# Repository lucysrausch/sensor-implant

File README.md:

# sensor-implant
WIP hardware design files for a sensor implant for my bachelors thesis.

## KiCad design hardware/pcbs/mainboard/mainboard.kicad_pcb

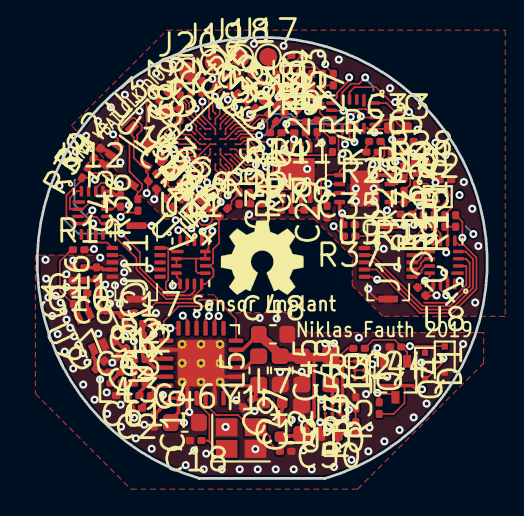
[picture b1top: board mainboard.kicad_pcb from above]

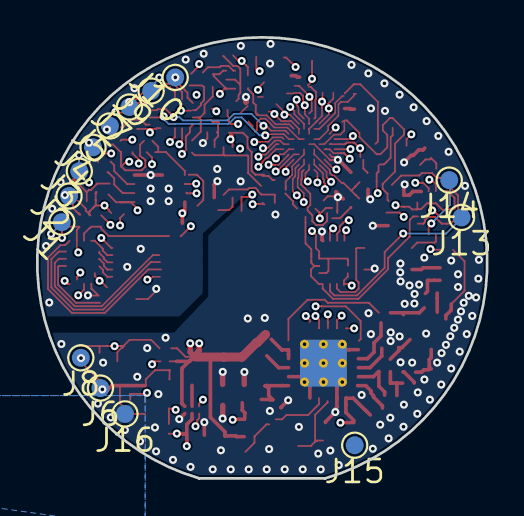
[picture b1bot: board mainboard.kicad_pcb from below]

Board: 4 copper layers, 25.0 x 24.5 mm, 142 parts (14 on the bottom side), 107 nets.

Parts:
C1, C15, C20, C21, C22, C23, C25, C26, C27, C29, C30, C31, C32, C38, C39, C40: 1n; C_0201_0603Metric
C2, C5, C24, C28, C34, C35, C37, C41, C42, C43, C44: 100n; C_0201_0603Metric
C3: 3p; C_0201_0603Metric
C4: 12p; C_0201_0603Metric
C6: 6.8p; C_0201_0603Metric
C7: DNP; C_0201_0603Metric
C8: 22p; C_0201_0603Metric
C9, C13, C16: 1u; C_0201_0603Metric
C10, C11: 3.3p; C_0201_0603Metric
C12, C17: 1.8p; C_0201_0603Metric
C14: 1p; C_0201_0603Metric
C18, C19: 18p; C_0201_0603Metric
C33, C36, C50: 1u; C_0402_1005Metric
C45, C46, C47, C48, C49: 10u; C_0603_1608Metric
D1: D; D_SC-80
D2: D_TVS; D_SC-80
J1, J2, J3, J4, J5, J6, J7, J8, J9, J10, J13, J14, J15, J16, J17, J18, J19, J20: PAD; TestPoint_Pad_D1.0mm
J11, J12: Conn_02x05_Odd_Even_MountingPin; DF37NB10DS04V53
L1: 47n; L_0201_0603Metric
L2: FERRET; L_0402_1005Metric
L3: 2.7n; L_0201_0603Metric
L4, L6: 9.1n; L_0201_0603Metric
L5: 15u; L_0603_1608Metric
L7: DNP; L_0402_1005Metric
L8: 18n; L_0201_0603Metric
L9: 2u2; L_0603_1608Metric
Q1, Q2, Q3: CSD75208W1015; WLCSP-6_1.4x1.0mm_P0.4mm
Q4: 2N7002; SOT-323_SC-70
R1, R2, R3, R5, R8, R10, R14, R15, R16, R18, R19, R23, R27, R30, R33, R36, R37, R38: 100; R_0201_0603Metric
R4, R11, R17, R26, R34, R35, R39, R42: 10k; R_0201_0603Metric
R6, R9, R12, R21, R25, R28: 200k; R_0201_0603Metric
R7, R13, R22, R29, R40: 2k; R_0201_0603Metric
R20, R24, R31, R32: 10M; R_0201_0603Metric
R41, R43: DNP; R_0201_0603Metric
U1: SX1261; QFN-24-1EP_4x4mm_P0.5mm_EP2.6x2.6mm_ThermalVias
U2: PE4259; SOT-363_SC-70-6
U3: REF3020; SOT-323_SC-70
U4: STM32L072CBYx; ST_WLCSP-49_Die447
U5, U8, U11, U12: TMUX1209; QFN40P260X180X55-16N
U6, U9: LPV542; WSON-8-1EP_3x3mm_P0.5mm_EP1.6x2.0mm
U7: LMT70; WLCSP-4_1.0x1.0mm_P0.4mm
U10: TPS61099; WLCSP-6_1.4x1.0mm_P0.4mm_hdi
U13: OPA333xxDCK; SOT-353_SC-70-5
Y1: 32MHz; Crystal_SMD_EuroQuartz_X22-4Pin_2.5x2.0mm

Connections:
+5VA: C24.1, C33.1, C34.1, C35.1, C42.1, C43.1, C50.1, R34.1, U3.1, U5.12, U5.16, U6.8, U7.A2, U8.12, U8.16, U9.8, U10.B2, U11.2, U11.3, U11.9, U11.11, U11.12, U12.2, U12.11, U12.12, U12.16, U13.5
+BATT: J6.1, Q3.B1, Q3.B2, Q3.C1, R31.1
ADC_IN0: C22.1, R10.2, U4.E5
ADC_IN1: C23.1, R14.2, U4.E4
ADC_IN2: C25.1, R15.2, U4.F6
ADC_IN3: C26.1, R27.2, U4.G7
ADC_IN6: C39.1, R19.2, U4.G5
ADC_IN7: C30.1, R37.2, U4.F4
ADC_IN8: C31.1, R30.2, U4.G4
ADC_IN9: C32.1, R38.2, U4.D3
ADC_IN10: C38.1, R36.2, U4.C5
ADC_IN11: C28.1, R20.2, R24.1, R40.1, U4.C4
ADC_IN12: C40.1, R33.2, U4.E7
AFE_EN: U4.E1, U10.C1
ANT_SW: R1.2, U4.B7
COIL: D1.2, J8.1
DAC_OUT1: R12.2, R28.2, U4.F5
DAC_OUT2: U4.G6, U13.1
DIO2: R2.1, U1.12
ELEC1: J11.9, U11.6
ELEC2: J13.1, U11.7
ELEC_SNS1: R36.1, U11.4, U11.5, U12.3
ELEC_SNS2: R38.1, U11.8, U11.10, U12.10
GNDD: C1.2, C2.2, C5.2, C6.2, C7.2, C9.2, C10.2, C11.2, C13.2, C14.2, C15.2, C16.2, C17.2, C18.2, C19.2, C21.1, C22.2, C23.2, C24.2, C25.2, C26.2, C28.2, C29.1, C30.2, C31.2, C32.2, C33.2, C34.2, C35.2, C36.2, C37.2, C38.2, C39.2, C40.2, C41.2, C42.2, C43.2, C44.2, C45.2, C46.2, C47.2, C48.2, C49.2, C50.2, D2.2, J11.2, J11.3, J11.6, J11.MP, J12.10, J12.MP, J16.1, J20.1, Q4.2, R6.2, R21.2, R24.2, R35.2, R42.2, U1.2, U1.5, U1.8, U1.20, U1.25, U2.2, U3.3, U4.A5, U4.D4, U5.13, U6.4, U7.A1, U8.13, U9.4, U10.A2, U11.13, U12.13, U13.2, Y1.2, Y1.4
ISFET1_D: R17.1, R23.1, R37.1, U8.7
ISFET1_D1: J12.1, U8.11
ISFET1_D2: J12.3, U8.10
ISFET1_D3: J12.5, U8.9
ISFET1_D4: J12.7, U8.8
ISFET1_S: C27.1, J12.9, R10.1, R26.2, R29.1, U9.7
ISFET1_SHNT: Q2.A1, Q2.A2, Q2.C1, R19.1, R23.2, R43.1
ISFET2_D: R4.1, R8.1, R27.1, U5.7
ISFET2_D2: J1.1, U5.10
ISFET2_D3: J2.1, U5.9
ISFET2_D4: J3.1, U5.8
ISFET2_S: C20.1, J4.1, R11.2, R13.1, R14.1, U6.7
ISFET2_SHNT: Q1.A1, Q1.A2, Q1.C1, R8.2, R30.1, R41.1
MUX1IN0: U4.F2, U8.15
MUX1IN1: U4.G1, U8.14
MUX2IN0: U4.G3, U5.15
MUX2IN1: U4.F3, U5.14
MUX3EN: U4.E2, U11.16
MUX3IN0: U4.C7, U11.15
MUX3IN1: U4.C1, U11.14
MUX4IN0: U4.A6, U12.15
MUX4IN1: U4.B5, U12.14
unnamed: C1.1, R1.1, U2.6
unnamed: C2.1, L1.1, U1.24
unnamed: C3.1, C4.2, C6.1, L3.2
unnamed: C3.2, L1.2, L3.1, U1.23
unnamed: C4.1, L4.1
unnamed: C5.1, U4.D5
unnamed: C7.1, L4.2, U2.1
unnamed: C8.2, U2.5
unnamed: C9.1, L5.1, L7.1, U1.7
unnamed: C8.1, C10.1, L6.1
unnamed: C12.1, C14.1, U2.3
unnamed: C12.2, L8.1, U1.22
unnamed: C13.1, U3.2, U4.E6
unnamed: C15.1, R2.2, U2.4
unnamed: C16.1, C46.1, L2.1, L7.2, U1.1
unnamed: C17.1, L8.2, U1.21
unnamed: C18.1, U1.3, Y1.1
unnamed: C19.1, U1.4, Y1.3
unnamed: C20.2, R4.2, U6.6
unnamed: C21.2, R9.2, R11.1, U6.5
unnamed: C27.2, R17.2, U9.6
unnamed: C29.2, R25.2, R26.1, U9.5
unnamed: L5.2, U1.9
unnamed: L9.2, U10.B1
unnamed: Q1.B1, Q1.B2, R3.1, R41.2
unnamed: Q1.C2, R5.2
unnamed: Q2.B1, Q2.B2, R16.1, R43.2
unnamed: Q2.C2, R18.2
unnamed: Q3.A2, Q4.3, R31.2
unnamed: R3.2, R7.1, R9.1, U6.1
unnamed: R6.1, R7.2, U6.2
unnamed: R12.1, R13.2, U6.3
unnamed: R16.2, R22.1, R25.1, U9.1
unnamed: R21.1, R22.2, U9.2
unnamed: R28.1, R29.2, U9.3
unnamed: R34.2, R35.1, U10.C2
unnamed: R39.2, R42.1, U13.3
unnamed: R40.2, U7.B1
O2_ELEC1: J11.10, U12.6
O2_ELEC2: J14.1, U12.7
O2_FORCE: R39.1, U12.4, U12.9, U13.4
REFFET1_D: J12.2, R15.1, R18.1, U8.6
REFFET1_D2: J12.8, U8.3
REFFET1_D3: J12.6, U8.4
REFFET1_D4: J12.4, U8.5
REFFET2_D: J5.1, R5.1, R33.1, U5.6
REFFET2_D2: J7.1, U5.3
REFFET2_D3: J9.1, U5.4
REFFET2_D4: J10.1, U5.5
RF_ANT: C11.1, J11.4, L6.2
RF_BUSY: U1.14, U4.D2
RF_CS: U1.19, U4.A2
RF_MISO: U1.16, U4.B3
RF_MOSI: U1.17, U4.A4
RF_RST: U1.15, U4.D1
RF_SCK: U1.18, U4.A3
SWCLK: J18.1, U4.B2
SWDIO: J17.1, U4.C2
TAG_EN: C44.1, D1.1, D2.1, Q4.1, R32.1, U4.F1
T_EN: U4.B1, U7.B2
VCC: C36.1, C37.1, C41.1, C45.1, C47.1, C48.1, C49.1, J19.1, L2.2, L9.1, Q3.A1, R20.1, R32.2, U1.10, U1.11, U4.A7, U4.B6, U4.F7, U4.G2, U10.A1

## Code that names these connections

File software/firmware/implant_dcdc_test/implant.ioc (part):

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Mcu.Name=STM32L072C(B-Z)Yx
Mcu.Package=WLCSP49
Mcu.UserName=STM32L072CBYx
PA0.Mode=IN0
PA0.Signal=ADC_IN0
PA1.Mode=IN1
PA1.Signal=ADC_IN1
PA10.GPIOParameters=GPIO_Label
PA10.GPIO_Label=MUX3IN1
PA10.Signal=GPIO_Output
PA11.GPIOParameters=GPIO_Label
PA11.GPIO_Label=BUSY
PA11.Signal=GPIO_Input
PA12.GPIOParameters=GPIO_Label
PA12.GPIO_Label=TEMPEN
PA12.Signal=GPIO_Output
PA13.Mode=Serial_Wire
PA13.Signal=SYS_SWDIO
PA14.Mode=Serial_Wire
PA14.Signal=SYS_SWCLK
PA15.Mode=NSS_Signal_Hard_Output
PA15.Signal=SPI1_NSS
PA2.Mode=IN2
PA2.Signal=ADC_IN2
PA3.Mode=IN3
PA3.Signal=ADC_IN3
PA4.Signal=COMP_DAC1_group
PA5.Signal=COMP_DAC2_group
PA6.Mode=IN6
PA6.Signal=ADC_IN6
PA7.Mode=IN7
PA7.Signal=ADC_IN7
PA8.GPIOParameters=GPIO_Label
PA8.GPIO_Label=RESET
PA8.Signal=GPIO_Output
PA9.GPIOParameters=GPIO_Label
PA9.GPIO_Label=MUX3EN
PA9.Signal=GPIO_Output
PB0.Mode=IN8
PB0.Signal=ADC_IN8
PB1.Mode=IN9
PB1.Signal=ADC_IN9
PB10.GPIOParameters=GPIO_Label
PB10.GPIO_Label=MUX2IN0
PB10.Signal=GPIO_Output
PB11.GPIOParameters=GPIO_Label
PB11.GPIO_Label=MUX2IN1
PB11.Signal=GPIO_Output
PB12.GPIOParameters=GPIO_Label
PB12.GPIO_Label=MUX1IN1
PB12.Signal=GPIO_Output
PB13.GPIOParameters=GPIO_Label
PB13.GPIO_Label=MUX1IN0
PB13.Signal=GPIO_Output
PB14.GPIOParameters=PinState,GPIO_Label,GPIO_ModeDefaultOutputPP
PB14.GPIO_Label=TAGEN
PB14.GPIO_ModeDefaultOutputPP=GPIO_MODE_OUTPUT_OD
PB14.PinState=GPIO_PIN_SET
PB14.Signal=GPIO_Output
PB15.GPIOParameters=GPIO_Label
PB15.GPIO_Label=AFEEN
PB15.Signal=GPIO_Output
PB3.Mode=Full_Duplex_Master
PB3.Signal=SPI1_SCK
PB4.Mode=Full_Duplex_Master
PB4.Signal=SPI1_MISO
PB5.Mode=Full_Duplex_Master
PB5.Signal=SPI1_MOSI
PB8.GPIOParameters=GPIO_Label
PB8.GPIO_Label=MUX4IN1
PB8.Signal=GPIO_Output
PB9.GPIOParameters=GPIO_Label
PB9.GPIO_Label=MUX4IN0
PB9.Signal=GPIO_Output
PC0.Mode=IN10
PC0.Signal=ADC_IN10
PC1.Mode=IN11
PC1.Signal=ADC_IN11
PC13.GPIOParameters=GPIO_Label
PC13.GPIO_Label=ANTSW
PC13.Signal=GPIO_Output
PC15-OSC32_OUT.GPIOParameters=GPIO_Label
PC15-OSC32_OUT.GPIO_Label=MUX3IN0
PC15-OSC32_OUT.Signal=GPIO_Output
PC2.Mode=IN12
PC2.Signal=ADC_IN12
RCC.HSE_VALUE=8000000
RCC.SYSCLKFreq_VALUE=4000000
RCC.SYSCLKSource=RCC_SYSCLKSOURCE_HSI
board=implant

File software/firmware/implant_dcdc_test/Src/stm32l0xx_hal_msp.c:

/**
  ******************************************************************************
  * File Name          : stm32l0xx_hal_msp.c
  * Description        : This file provides code for the MSP Initialization 
  *                      and de-Initialization codes.
  ******************************************************************************
  ** This notice applies to any and all portions of this file
  * that are not between comment pairs USER CODE BEGIN and
  * USER CODE END. Other portions of this file, whether 
  * inserted by the user or by software development tools
  * are owned by their respective copyright owners.
  *
  * COPYRIGHT(c) 2019 STMicroelectronics
  *
  * Redistribution and use in source and binary forms, with or without modification,
  * are permitted provided that the following conditions are met:
  *   1. Redistributions of source code must retain the above copyright notice,
  *      this list of conditions and the following disclaimer.
  *   2. Redistributions in binary form must reproduce the above copyright notice,
  *      this list of conditions and the following disclaimer in the documentation
  *      and/or other materials provided with the distribution.
  *   3. Neither the name of STMicroelectronics nor the names of its contributors
  *      may be used to endorse or promote products derived from this software
  *      without specific prior written permission.
  *
  * THIS SOFTWARE IS PROVIDED BY THE COPYRIGHT HOLDERS AND CONTRIBUTORS "AS IS"
  * AND ANY EXPRESS OR IMPLIED WARRANTIES, INCLUDING, BUT NOT LIMITED TO, THE
  * IMPLIED WARRANTIES OF MERCHANTABILITY AND FITNESS FOR A PARTICULAR PURPOSE ARE
  * DISCLAIMED. IN NO EVENT SHALL THE COPYRIGHT HOLDER OR CONTRIBUTORS BE LIABLE
  * FOR ANY DIRECT, INDIRECT, INCIDENTAL, SPECIAL, EXEMPLARY, OR CONSEQUENTIAL
  * DAMAGES (INCLUDING, BUT NOT LIMITED TO, PROCUREMENT OF SUBSTITUTE GOODS OR
  * SERVICES; LOSS OF USE, DATA, OR PROFITS; OR BUSINESS INTERRUPTION) HOWEVER
  * CAUSED AND ON ANY THEORY OF LIABILITY, WHETHER IN CONTRACT, STRICT LIABILITY,
  * OR TORT (INCLUDING NEGLIGENCE OR OTHERWISE) ARISING IN ANY WAY OUT OF THE USE
  * OF THIS SOFTWARE, EVEN IF ADVISED OF THE POSSIBILITY OF SUCH DAMAGE.
  *
  ******************************************************************************
  */
/* Includes ------------------------------------------------------------------*/
#include "stm32l0xx_hal.h"

extern void _Error_Handler(char *, int);
/* USER CODE BEGIN 0 */

/* USER CODE END 0 */
/**
  * Initializes the Global MSP.
  */
void HAL_MspInit(void)
{
  /* USER CODE BEGIN MspInit 0 */

  /* USER CODE END MspInit 0 */

  __HAL_RCC_SYSCFG_CLK_ENABLE();
  __HAL_RCC_PWR_CLK_ENABLE();

  /* System interrupt init*/
  /* SVC_IRQn interrupt configuration */
  HAL_NVIC_SetPriority(SVC_IRQn, 0, 0);
  /* PendSV_IRQn interrupt configuration */
  HAL_NVIC_SetPriority(PendSV_IRQn, 0, 0);
  /* SysTick_IRQn interrupt configuration */
  HAL_NVIC_SetPriority(SysTick_IRQn, 0, 0);

  /* USER CODE BEGIN MspInit 1 */

  /* USER CODE END MspInit 1 */
}

void HAL_ADC_MspInit(ADC_HandleTypeDef* hadc)
{

  GPIO_InitTypeDef GPIO_InitStruct;
  if(hadc->Instance==ADC1)
  {
  /* USER CODE BEGIN ADC1_MspInit 0 */

  /* USER CODE END ADC1_MspInit 0 */
    /* Peripheral clock enable */
    __HAL_RCC_ADC1_CLK_ENABLE();
  
    /**ADC GPIO Configuration    
    PC1     ------> ADC_IN11
    PC0     ------> ADC_IN10
    PB1     ------> ADC_IN9
    PA1     ------> ADC_IN1
    PA0     ------> ADC_IN0
    PC2     ------> ADC_IN12
    PA7     ------> ADC_IN7
    PA2     ------> ADC_IN2
    PB0     ------> ADC_IN8
    PA6     ------> ADC_IN6
    PA3     ------> ADC_IN3 
    */
    GPIO_InitStruct.Pin = GPIO_PIN_1|GPIO_PIN_0|GPIO_PIN_2;
    GPIO_InitStruct.Mode = GPIO_MODE_ANALOG;
    GPIO_InitStruct.Pull = GPIO_NOPULL;
    HAL_GPIO_Init(GPIOC, &GPIO_InitStruct);

    GPIO_InitStruct.Pin = GPIO_PIN_1|GPIO_PIN_0;
    GPIO_InitStruct.Mode = GPIO_MODE_ANALOG;
    GPIO_InitStruct.Pull = GPIO_NOPULL;
    HAL_GPIO_Init(GPIOB, &GPIO_InitStruct);

    GPIO_InitStruct.Pin = GPIO_PIN_1|GPIO_PIN_0|GPIO_PIN_7|GPIO_PIN_2 
                          |GPIO_PIN_6|GPIO_PIN_3;
    GPIO_InitStruct.Mode = GPIO_MODE_ANALOG;
    GPIO_InitStruct.Pull = GPIO_NOPULL;
    HAL_GPIO_Init(GPIOA, &GPIO_InitStruct);

  /* USER CODE BEGIN ADC1_MspInit 1 */

  /* USER CODE END ADC1_MspInit 1 */
  }

}

void HAL_ADC_MspDeInit(ADC_HandleTypeDef* hadc)
{

  if(hadc->Instance==ADC1)
  {
  /* USER CODE BEGIN ADC1_MspDeInit 0 */

  /* USER CODE END ADC1_MspDeInit 0 */
    /* Peripheral clock disable */
    __HAL_RCC_ADC1_CLK_DISABLE();
  
    /**ADC GPIO Configuration    
    PC1     ------> ADC_IN11
    PC0     ------> ADC_IN10
    PB1     ------> ADC_IN9
    PA1     ------> ADC_IN1
    PA0     ------> ADC_IN0
    PC2     ------> ADC_IN12
    PA7     ------> ADC_IN7
    PA2     ------> ADC_IN2
    PB0     ------> ADC_IN8
    PA6     ------> ADC_IN6
    PA3     ------> ADC_IN3 
    */
    HAL_GPIO_DeInit(GPIOC, GPIO_PIN_1|GPIO_PIN_0|GPIO_PIN_2);

    HAL_GPIO_DeInit(GPIOB, GPIO_PIN_1|GPIO_PIN_0);

    HAL_GPIO_DeInit(GPIOA, GPIO_PIN_1|GPIO_PIN_0|GPIO_PIN_7|GPIO_PIN_2 
                          |GPIO_PIN_6|GPIO_PIN_3);

  /* USER CODE BEGIN ADC1_MspDeInit 1 */

  /* USER CODE END ADC1_MspDeInit 1 */
  }

}

void HAL_DAC_MspInit(DAC_HandleTypeDef* hdac)
{

  GPIO_InitTypeDef GPIO_InitStruct;
  if(hdac->Instance==DAC)
  {
  /* USER CODE BEGIN DAC_MspInit 0 */

  /* USER CODE END DAC_MspInit 0 */
    /* Peripheral clock enable */
    __HAL_RCC_DAC_CLK_ENABLE();
  
    /**DAC GPIO Configuration    
    PA4     ------> DAC_OUT1
    PA5     ------> DAC_OUT2 
    */
    GPIO_InitStruct.Pin = GPIO_PIN_4|GPIO_PIN_5;
    GPIO_InitStruct.Mode = GPIO_MODE_ANALOG;
    GPIO_InitStruct.Pull = GPIO_NOPULL;
    HAL_GPIO_Init(GPIOA, &GPIO_InitStruct);

  /* USER CODE BEGIN DAC_MspInit 1 */

  /* USER CODE END DAC_MspInit 1 */
  }

}

void HAL_DAC_MspDeInit(DAC_HandleTypeDef* hdac)
{

  if(hdac->Instance==DAC)
  {
  /* USER CODE BEGIN DAC_MspDeInit 0 */

  /* USER CODE END DAC_MspDeInit 0 */
    /* Peripheral clock disable */
    __HAL_RCC_DAC_CLK_DISABLE();
  
    /**DAC GPIO Configuration    
    PA4     ------> DAC_OUT1
    PA5     ------> DAC_OUT2 
    */
    HAL_GPIO_DeInit(GPIOA, GPIO_PIN_4|GPIO_PIN_5);

  /* USER CODE BEGIN DAC_MspDeInit 1 */

  /* USER CODE END DAC_MspDeInit 1 */
  }

}

void HAL_SPI_MspInit(SPI_HandleTypeDef* hspi)
{

  GPIO_InitTypeDef GPIO_InitStruct;
  if(hspi->Instance==SPI1)
  {
  /* USER CODE BEGIN SPI1_MspInit 0 */

  /* USER CODE END SPI1_MspInit 0 */
    /* Peripheral clock enable */
    __HAL_RCC_SPI1_CLK_ENABLE();
  
    /**SPI1 GPIO Configuration    
    PA15     ------> SPI1_NSS
    PB3     ------> SPI1_SCK
    PB5     ------> SPI1_MOSI
    PB4     ------> SPI1_MISO 
    */
    GPIO_InitStruct.Pin = GPIO_PIN_15;
    GPIO_InitStruct.Mode = GPIO_MODE_AF_PP;
    GPIO_InitStruct.Pull = GPIO_NOPULL;
    GPIO_InitStruct.Speed = GPIO_SPEED_FREQ_VERY_HIGH;
    GPIO_InitStruct.Alternate = GPIO_AF0_SPI1;
    HAL_GPIO_Init(GPIOA, &GPIO_InitStruct);

    GPIO_InitStruct.Pin = GPIO_PIN_3|GPIO_PIN_5|GPIO_PIN_4;
    GPIO_InitStruct.Mode = GPIO_MODE_AF_PP;
    GPIO_InitStruct.Pull = GPIO_NOPULL;
    GPIO_InitStruct.Speed = GPIO_SPEED_FREQ_VERY_HIGH;
    GPIO_InitStruct.Alternate = GPIO_AF0_SPI1;
    HAL_GPIO_Init(GPIOB, &GPIO_InitStruct);

  /* USER CODE BEGIN SPI1_MspInit 1 */

  /* USER CODE END SPI1_MspInit 1 */
  }

}

void HAL_SPI_MspDeInit(SPI_HandleTypeDef* hspi)
{

  if(hspi->Instance==SPI1)
  {
  /* USER CODE BEGIN SPI1_MspDeInit 0 */

  /* USER CODE END SPI1_MspDeInit 0 */
    /* Peripheral clock disable */
    __HAL_RCC_SPI1_CLK_DISABLE();
  
    /**SPI1 GPIO Configuration    
    PA15     ------> SPI1_NSS
    PB3     ------> SPI1_SCK
    PB5     ------> SPI1_MOSI
    PB4     ------> SPI1_MISO 
    */
    HAL_GPIO_DeInit(GPIOA, GPIO_PIN_15);

    HAL_GPIO_DeInit(GPIOB, GPIO_PIN_3|GPIO_PIN_5|GPIO_PIN_4);

  /* USER CODE BEGIN SPI1_MspDeInit 1 */

  /* USER CODE END SPI1_MspDeInit 1 */
  }

}

/* USER CODE BEGIN 1 */

/* USER CODE END 1 */

/**
  * @}
  */

/**
  * @}
  */

/************************ (C) COPYRIGHT STMicroelectronics *****END OF FILE****/

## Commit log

2019-05-17 finished routing
2019-09-18 release
2019-09-18 Create LICENSE
2019-09-18 Added files for v2
2019-09-18 Added files for v3
2019-09-18 Added files for v4
2019-09-18 Added files for the test setup
2019-09-18 Added bachelor thesis
2019-09-18 Readded STZ logo
2019-09-18 Added missing design files
2019-09-18 Added basic testing firmware
